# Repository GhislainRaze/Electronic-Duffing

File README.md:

# An electronic Duffing oscillator

## Overview
This repository contains files for the realization of an electronic Duffing oscillator, i.e., a circuit whose behavior is governed Duffing's equation

$\qquad m\ddot{x}(t) + c\dot{x}(t) + kx(t) + k_3 x^3(t) = f_{ext}(t),$
    
with $m>0$, $c\geq0$ and $k_3\geq0$.

The circuit takes a signal proportional to $f_{ext}$ as input and outputs signals proportional to $x$ and $\dot{x}$. It allows for tunable values of the parameters $c$, $k$ and $k_3$ via the use of potentiometers. It is also possible to chose positive or negative values for $k$ and obtain a single- or double-well oscillator, respectively.

The circuit requires an external power source with symmetric supplies. The input and output signals can be imposed/measured with BNC connectors.

## References

The circuit diagrams were realized using KiCad7.0 (https://www.kicad.org/), inspired from the following works:

\[1\] B. K. Jones and G. Trefan, “The Duffing oscillator: A precise electronic analog chaos demonstrator for the undergraduate laboratory,” Am. J. Phys., vol. 69, no. 4, pp. 464–469, Apr. 2001, doi: [10.1119/1.1336838](https://doi.org/10.1119/1.1336838).

\[2\] K. Srinivasan, K. Thamilmaran, and A. Venkatesan, “Effect of nonsinusoidal periodic forces in Duffing oscillator: Numerical and analog simulation studies,” Chaos, Solitons & Fractals, vol. 40, no. 1, pp. 319–330, Apr. 2009, doi: [10.1016/j.chaos.2007.07.090](https://doi.org/10.1016/j.chaos.2007.07.090).

## More information

For more infomation, see the [documentation file](DOC/Electronic_Duffing.pdf).

## License

<p xmlns:cc="http://creativecommons.org/ns#" >This work is licensed under <a href="http://creativecommons.org/licenses/by/4.0/?ref=chooser-v1" target="_blank" rel="license noopener noreferrer" style="display:inline-block;">CC BY 4.0</a></p>

## Disclaimer

It is believed by the author that the design does not violate the Copyright of any other party. This cannot be guaranteed however, and the author accepts no liability for loss or damages that may be imposed upon the user by any Court of Law, statutory or other body, should it transpire that a similar circuit has been simultaneously or previously designed, published or patented by another party.

The author cannot be held responsible for any issues or damages either to life or property, or as monetary or physical losses, that might occur during the use of this circuit, either due to negligence, ignorance or lack of proper knowledge about the subject. It is entirely the user’s responsibility to determine the suitability of this design for the intended purpose, and to take enough precautions before assembling and using the circuit.

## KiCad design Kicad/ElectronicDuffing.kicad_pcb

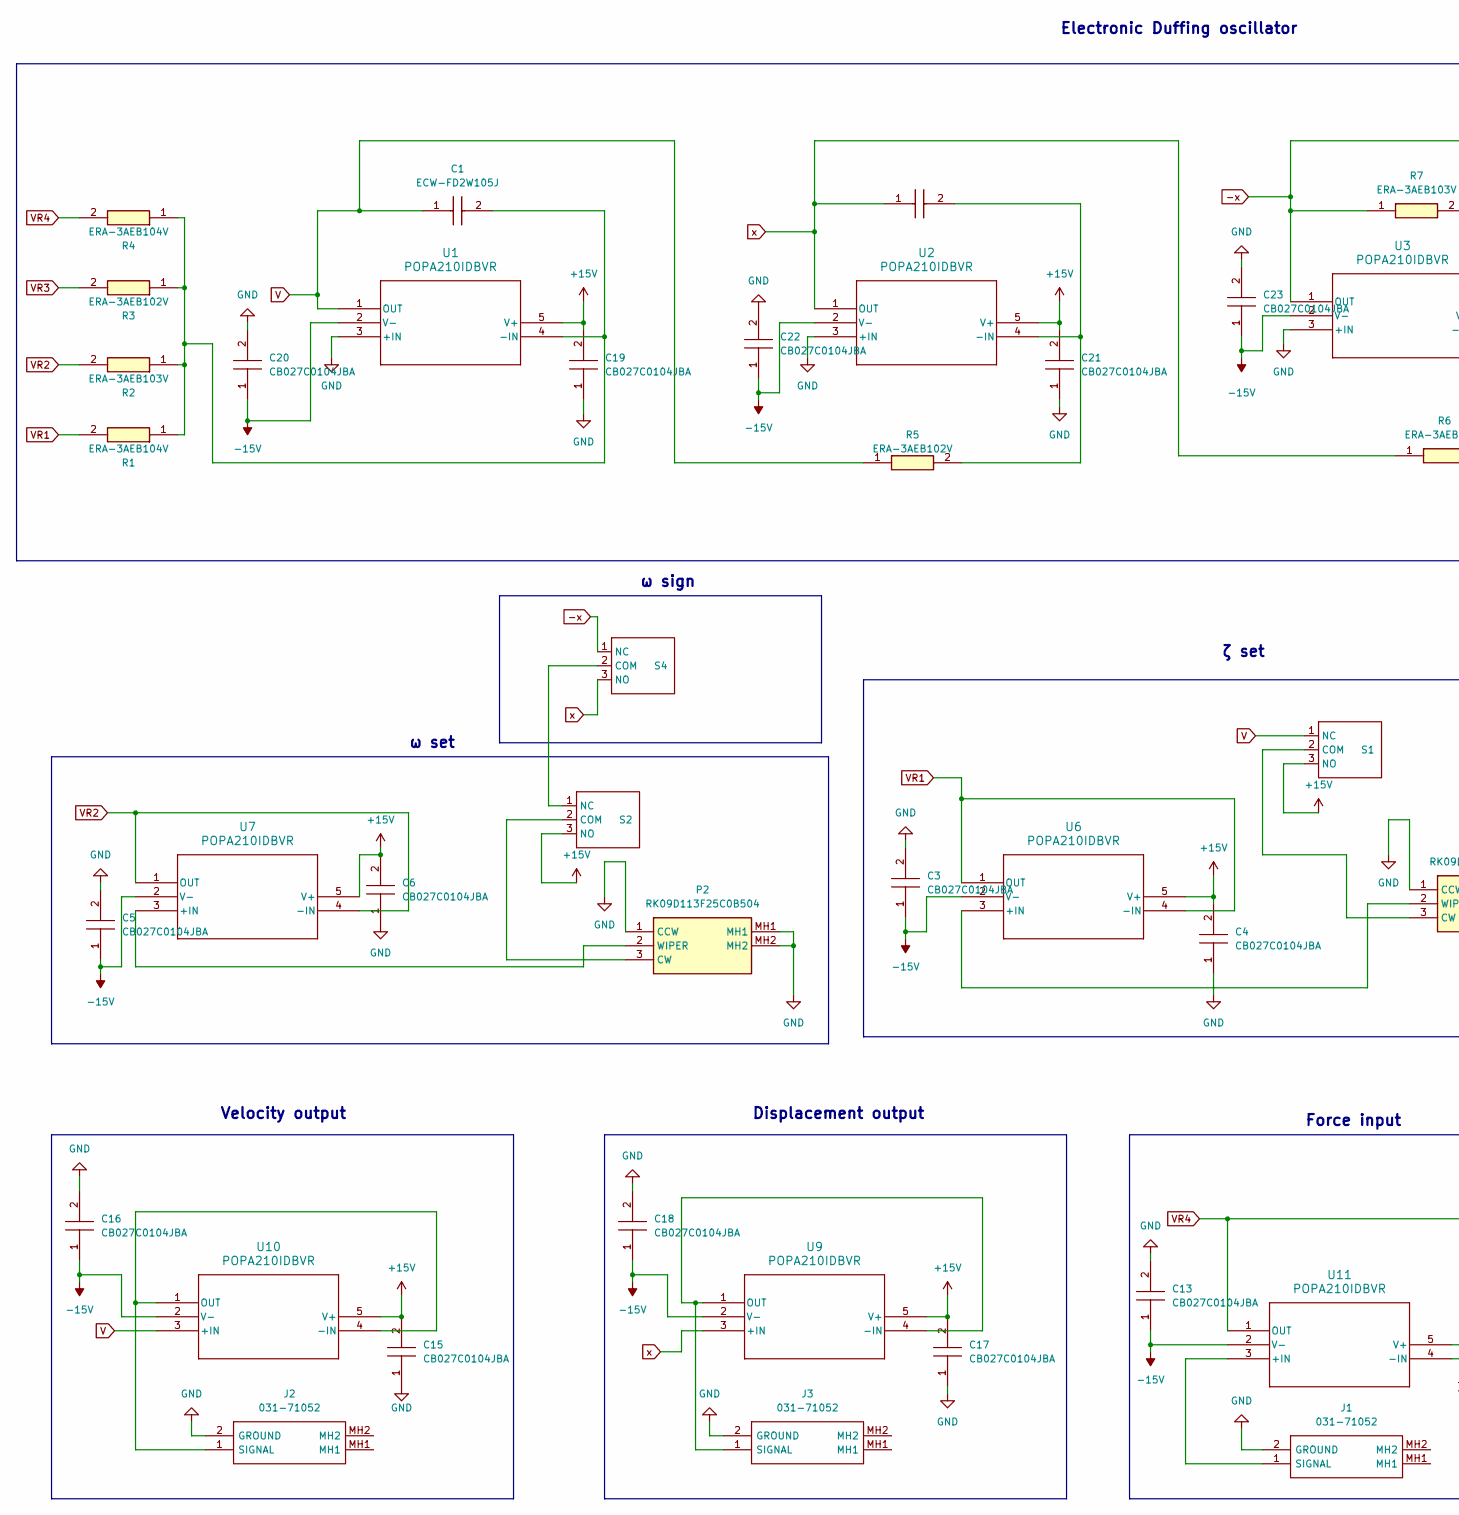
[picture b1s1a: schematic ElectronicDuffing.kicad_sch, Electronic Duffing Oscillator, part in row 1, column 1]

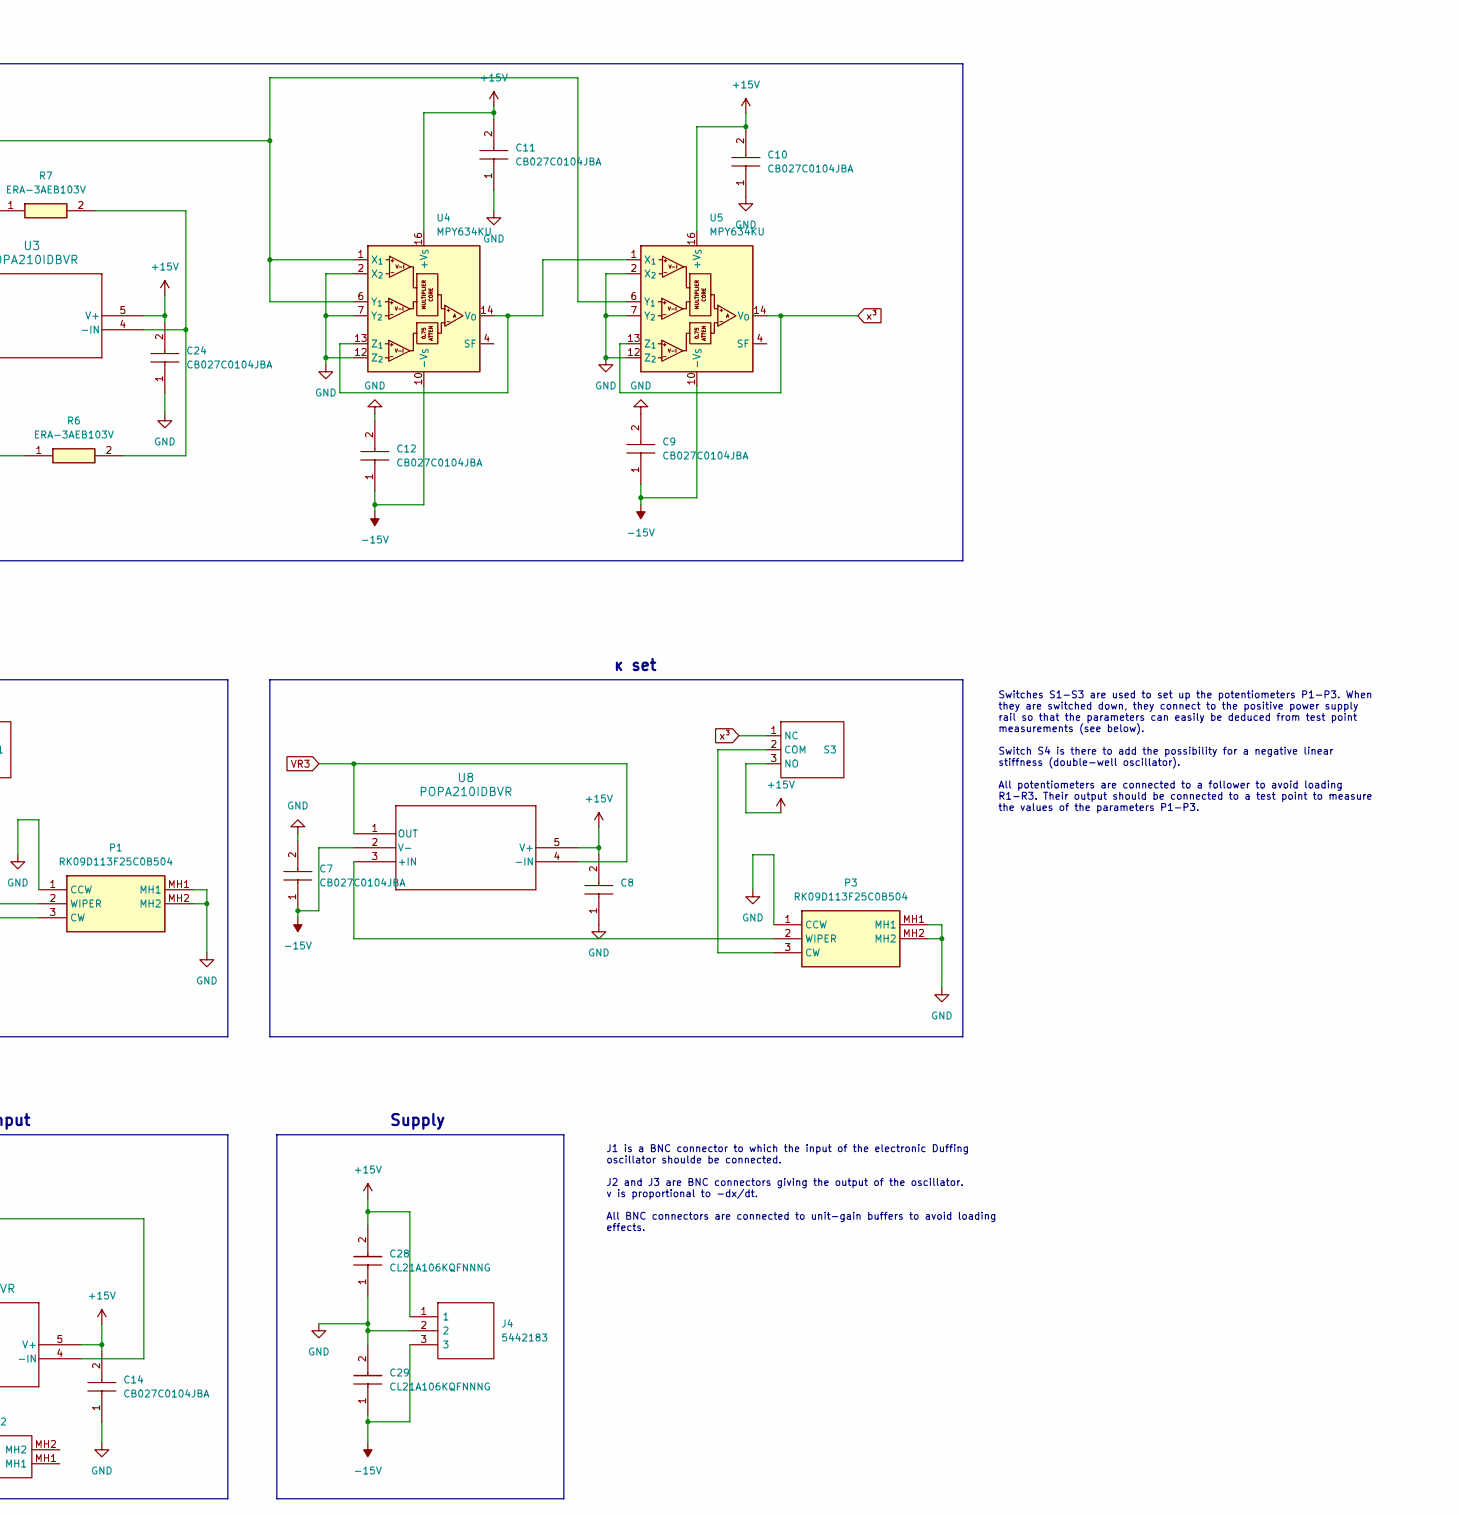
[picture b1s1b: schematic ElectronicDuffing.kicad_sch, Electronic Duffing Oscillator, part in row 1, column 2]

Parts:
C1, C2: ECW-FD2W105J; ECWFD2W105J; Mouser Part Number 667-ECW-FD2W105J
C3, C4, C5, C6, C7, C8, C9, C10, C11, C12, C13, C14, C15, C16, C17, C18, C19, C20, C21, C22, C23, C24: CB027C0104JBA; CAPC3325X230N; Mouser Part Number 581-CB027C0104JBA
C28, C29: CL21A106KQFNNNG; CAPC2012X135N; Mouser Part Number 187-CL21A106KQFNNNG
J1, J2, J3: 031-71052; 03171052; Manufacturer_Part_Number 031-71052
J4: 5442183; Mouser Part Number 651-5442183
P1, P2, P3: RK09D113F25C0B504; Mouser Part Number 688-RK09D113F25-500K
R1, R4: ERA-3AEB104V; ERA3AEB101V; Mouser Part Number 667-ERA-3AEB104V
R2, R6, R7: ERA-3AEB103V; ERA3AEB101V; Mouser Part Number 667-ERA-3AEB103V
R3, R5: ERA-3AEB102V; ERA3AEB101V; Mouser Part Number 667-ERA-3AEB102V
S1, S2, S3, S4: MFP120
U1, U2, U3, U6, U7, U8, U9, U10, U11: POPA210IDBVR; SOT23_DBV_TEX
U4, U5: MPY634KU; SOIC-16W_7.5x10.3mm_P1.27mm

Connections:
+15V: C4.2, C6.2, C8.2, C10.2, C11.2, C14.2, C15.2, C17.2, C19.2, C21.2, C24.2, C28.2, J4.1, S1.3 (NO), S2.3 (NO), S3.3 (NO), U1.5 (V+), U2.5 (V+), U3.5 (V+), U4.16 (+V_{S}), U5.16 (+V_{S}), U6.5 (V+), U7.5 (V+), U8.5 (V+), U9.5 (V+), U10.5 (V+), U11.5 (V+)
-15V: C3.1, C5.1, C7.1, C9.1, C12.1, C13.1, C16.1, C18.1, C20.1, C22.1, C23.1, C29.1, J4.3, U1.2 (V-), U2.2 (V-), U3.2 (V-), U4.10 (-V_{S}), U5.10 (-V_{S}), U6.2 (V-), U7.2 (V-), U8.2 (V-), U9.2 (V-), U10.2 (V-), U11.2 (V-)
-x: R7.1, S4.1 (NC), U3.1 (OUT), U4.1 (X_{1}), U4.6 (Y_{1}), U5.6 (Y_{1})
GND: C3.2, C4.1, C5.2, C6.1, C7.2, C8.1, C9.2, C10.1, C11.1, C12.2, C13.2, C14.1, C15.1, C16.2, C17.1, C18.2, C19.1, C20.2, C21.1, C22.2, C23.2, C24.1, C28.1, C29.2, J1.2 (GROUND), J2.2 (GROUND), J3.2 (GROUND), J4.2, P1.1 (CCW), P1.MH1, P1.MH2, P2.1 (CCW), P2.MH1, P2.MH2, P3.1 (CCW), P3.MH1, P3.MH2, U1.3 (+IN), U2.3 (+IN), U3.3 (+IN), U4.2 (X_{2}), U4.7 (Y_{2}), U4.12 (Z_{2}), U5.2 (X_{2}), U5.7 (Y_{2}), U5.12 (Z_{2})
unnamed: J1.1 (SIGNAL), U11.3 (+IN)
unnamed: J2.1 (SIGNAL), U10.1 (OUT), U10.4 (-IN)
unnamed: J3.1 (SIGNAL), U9.1 (OUT), U9.4 (-IN)
unnamed: P1.3 (CW), S1.2 (COM)
unnamed: P1.2 (WIPER), U6.3 (+IN)
unnamed: P2.3 (CW), S2.2 (COM)
unnamed: P2.2 (WIPER), U7.3 (+IN)
unnamed: P3.3 (CW), S3.2 (COM)
unnamed: P3.2 (WIPER), U8.3 (+IN)
unnamed: S2.1 (NC), S4.2 (COM)
unnamed: C1.2, R1.1, R2.1, R3.1, R4.1, U1.4 (-IN)
unnamed: C2.2, R5.2, U2.4 (-IN)
unnamed: R6.2, R7.2, U3.4 (-IN)
unnamed: U4.13 (Z_{1}), U4.14 (V_{O}), U5.1 (X_{1})
V: C1.1, R5.1, S1.1 (NC), U1.1 (OUT), U10.3 (+IN)
VR1: R1.2, U6.1 (OUT), U6.4 (-IN)
VR2: R2.2, U7.1 (OUT), U7.4 (-IN)
VR3: R3.2, U8.1 (OUT), U8.4 (-IN)
VR4: R4.2, U11.1 (OUT), U11.4 (-IN)
x: C2.1, R6.1, S4.3 (NO), U2.1 (OUT), U9.3 (+IN)
x³: S3.1 (NC), U5.13 (Z_{1}), U5.14 (V_{O})

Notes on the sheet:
ω set
κ set
ω sign
Force input
J1 is a BNC connector to which the input of the electronic Duffing oscillator shoulde be connected. J2 and J3 are BNC connectors giving the output of the oscillator. v is proportional to -dx/dt. All BNC connectors are connected to unit-gain buffers to avoid loading effects.
Switches S1-S3 are used to set up the potentiometers P1-P3. When they are switched down, they connect to the positive power supply rail so that the parameters can easily be deduced from test point measurements (see below). Switch S4 is there to add the possibility for a negative linear stiffness (d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
ζ set
Supply
Displacement output
Velocity output
Electronic Duffing oscillator

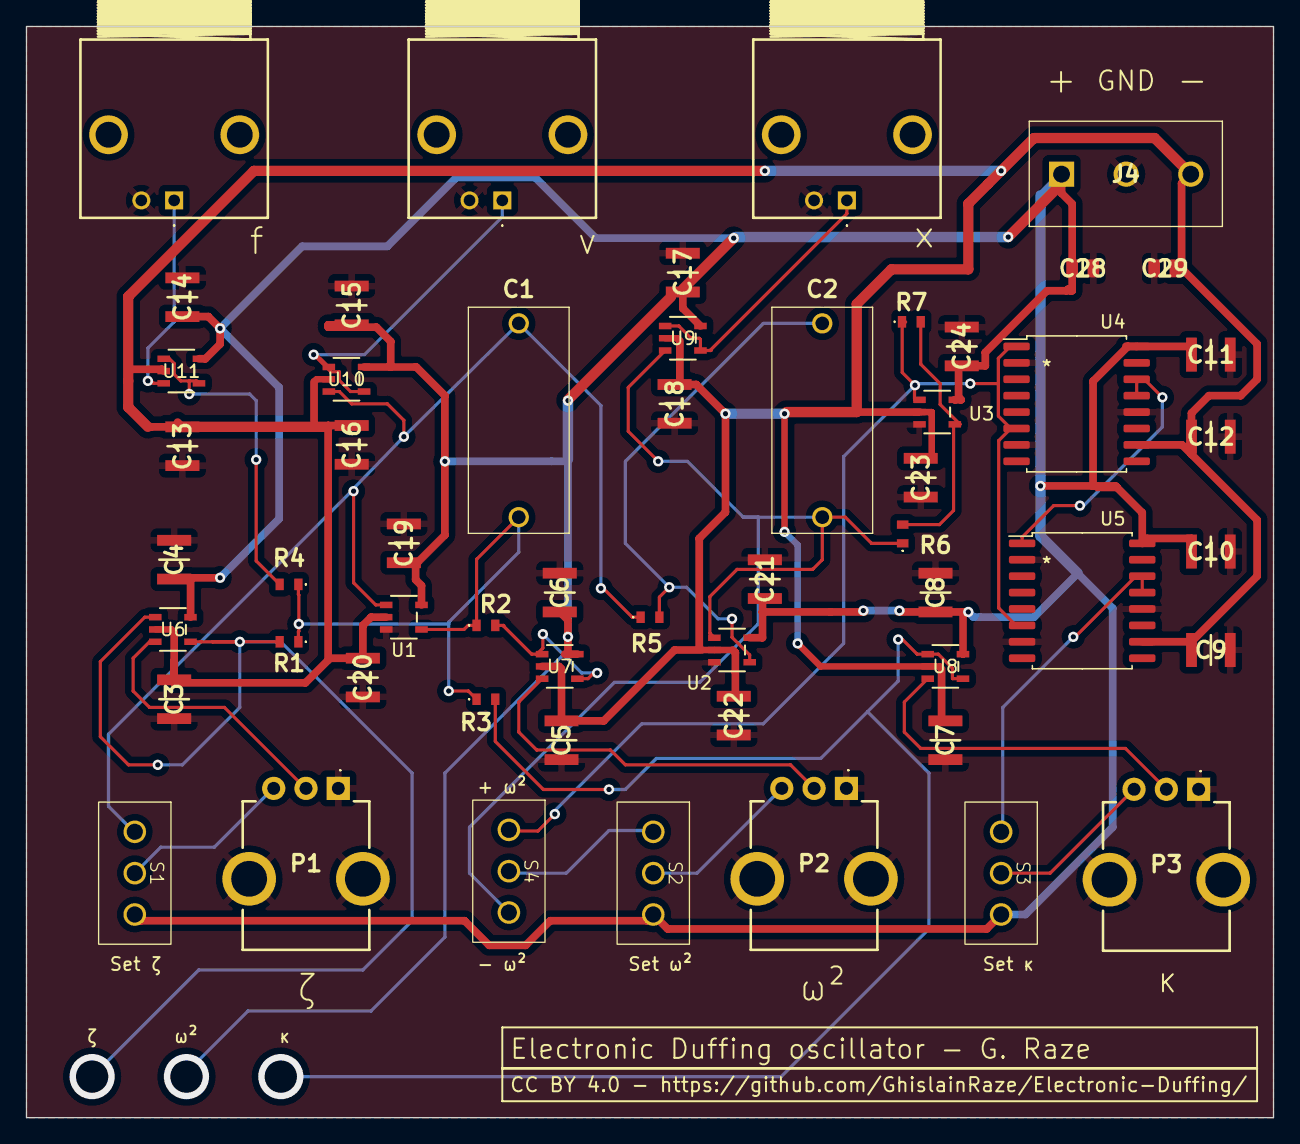
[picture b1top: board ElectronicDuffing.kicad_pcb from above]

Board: 2 copper layers, 96.5 x 84.5 mm, 55 parts (0 on the bottom side), 25 nets.

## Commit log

2024-05-02 Create doc
2024-05-02 Create kicad
2024-05-07 Ibom upload
2024-05-07 Create Tmp
2024-05-07 KiCad files upload
2024-05-07 Add Gerber files
2024-05-07 Upload libraries
2024-06-01 Rename Electronic_Duffing.pdf to Electronic_Duffing_2.pdf
2024-06-02 Rename Electronic_Duffing.pdf to DOC/Electronic_Duffing.pdf

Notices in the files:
Kicad/ElectronicDuffing.kicad_pcb:
CC BY 4.0 - https://github.com/GhislainRaze/Electronic-Duffing
